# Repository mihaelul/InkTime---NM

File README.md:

# InkTime - E-Paper Smartwatch Hardware Design

## 1. System Block Diagram
*This diagram illustrates the main hardware modules and their data/power connections to the central processing unit.*

```mermaid
graph TD

    ANTENNA[ANTENNA] ---|RF| SOC[nRF52840 <br> SoC]
    
    %% Peripherals and Interfaces
    SOC ---|I2C| IMU[IMU <br> SENSOR]
    SOC ---|SPI| EPD[E-PAPER <br> DISPLAY]
    SOC ---|PWM| SHAKER[SHAKER]
    SOC ---|GPIO| BTN[3X <br> BUTTON]
    SOC ---|SWD| DEBUG[DEBUG <br> SWD]

    USB[USB-C <br> CONNECTOR] ---|VUSB| CHARGER[CHARGER IC]
    CHARGER --- BATTERY[LI-PO BATTERY]
    CHARGER --- VREG[RT6160 <br> VOLTAGE <br> REGULATOR]
    BATTERY ---|VBAT| VREG

    %% 3V3 Power Rails
    VREG ---|3V3| IMU
    VREG ---|3V3| EPD
    VREG ---|3V3| SHAKER
```

## 1. Bill of Materials (BOM)

| Component | JLC Part # | Package | Description | Datasheet |
| :--- | :--- | :--- | :--- | :--- |
| **J1** | C122434 | SMD,P=0.5mm,Surface Mount，Right Angle | FFC & FPC Connectors 0.5mm FPC RA SMT Dual Contact 24Ckt | [datasheet](https://octopart.com/datasheet/tag-connect/TC2030-IDC) |
| **L1, L2, L3** | C12669 | 402 | Generic chip inductor | [datasheet](https://www.lcsc.com/datasheet/C12669.pdf) |
| **L5** | C1329646 | SMD,4.8x4.8mm | 1.6A 1.6A 4.7uH 41.4mΩ AEC-Q200 ±30% SMD,4.8x4.8mm Power Inductors ROHS | [datasheet](https://wmsc.lcsc.com/wmsc/upload/file/pdf/v2/lcsc/2304140030_BOURNS-SRR4828A-4R7Y_C1329646.pdf) |
| **IC3** | C189517 | LGA-12(2x2) | Accelerometers Triaxial low-g 12bit Acceleration Sensor | [datasheet](https://files.pine64.org/doc/datasheet/pinetime/BST-BMA421-FL000.pdf) |
| **Q1** | C2564 | TO-220AB | -55℃~+175℃ 1 P-Channel 180nC@10V 200W 20mΩ@10V 3.4nF 4V 55V 640pF 74A P-Channel TO-220AB MOSFETs ROHS | [datasheet](https://files.pine64.org/doc/datasheet/pinetime/BST-BMA421-FL000.pdf) |
| **U3** | C2682616 | DFN-8-EP(2x2) | -40℃~+85℃ 1 2.5V~4.5V 3uA I2C Lithium Battery DFN-8-EP(2x2) Battery Management ROHS | [datasheet](https://www.analog.com/en/products/max17048.html?ADICID=synd_ww_portfolio_pi_octopart_na_2024) |
| **ANT1** | C2917717 | 1206 | -45℃~+125℃ 0.5dBi 1.3mm 1.6mm 100MHz 2.45GHz 2W 3.2mm 50Ω Patch Antenna 1206 Antennas ROHS | [datasheet](https://www.alldatasheet.com/datasheet-pdf/pdf/348957/JOHANSON/2450AT18B100.html) |
| **D3** | C2969755 | SOT-23-6L | Low Cap. ESD Protection Auto SOT-23-6 STMicroelectronics USBLC6-2SC6Y, Dual Uni-Directional TVS Diode Array, 6-Pin SOT-23 | [datasheet](https://octopart.com/datasheet/stmicroelectronics/USBLC6-2SC6Y) |
| **X2** | C32346 | SMD3215-2P | -40℃~+85℃ 12.5pF 32.768kHz 70kΩ Crystal Oscillator ±20ppm SMD3215-2P Crystals ROHS | [datasheet](https://www.lcsc.com/datasheet/C32346.pdf) |
| **U1** | C3606653 | QFN-48(6x6) | nRF52840 | [datasheet](https://octopart.com/datasheet/nordic-semiconductor/NRF52840-QIAA-T) |
| **IC1** | C3682423 | DSBGA-8(1.1x1.6) | Charger IC Lithium Ion/Polymer, Lithium Iron Phosphate 8-DSBGA (1.6x1.1) | [datasheet](https://www.alldatasheet.com/datasheet-pdf/pdf/1359210/TI/BQ25180YBGR.html) |
| **R17-R18, R1_EP_DR, R1_USB, R2-R5, R7-R9, R_PWR_EPD, R_TYPE_SEL** | C3920633 | 0201 | 7.68k 0201 Thin Film Surface Mount Fixed Resistor +/-0.5% 870.031W CPF0201D7K68C1 |  |
| **Q3** | C469327 | SOT-323 | MOSFET N-Ch 30V 1.5A TrenchFET SC70 Vishay Si1308EDL-T1-GE3 N-channel MOSFET Transistor, 1.5 A, 30 V, 3-Pin SC-70 | [datasheet](https://4donline.ihs.com/images/VipMasterIC/IC/VISH/VISH-S-A0000692786/VISH-S-A0000692786-1.pdf?hkey=6D3A4C79FDBF58556ACFDE234799DDF0) |
| **SW_DN, SW_ENT, SW_UP** | C569760 | SMD,3.9x2.9mm | -40℃~+85℃ 1.6N 1.6mm 15V 2.9mm 20mA 3.9mm 500,000 Cycles IP67 J-Lead Rectangular Button SPST Surface Mount White With Bracket | [datasheet](https://wmsc.lcsc.com/wmsc/upload/file/pdf/v2/lcsc/2301111010_PANASONIC-EVPAKE31A_C569760.pdf) |
| **L7** | C5832368 | 1008 | 13mΩ 470nH 6.5A 7.5A ±20% 1008 Power Inductors ROHS | [datasheet](https://www.lcsc.com/datasheet/C5832368.pdf?spm=wm.sxq.inf.ggs&lcsc_vid=RQcLUgVXFFNXXwFeQQJaUQVXFgRWA1xUFlcIVABQQQQxVlNRQVZXXlBXQ1VfUjsOAxUeFF5JWBYZEEoBGA4JCwFIFA4DSA%3D%3D) |
| **IC9** | C7065276 | WLCSP-15B(2.3x1.4) | Buck-Boost Regulator Positive Output Step-Up/Step-Down I2C DC-DC Controller IC 15-WL-CSP | [datasheet](https://www.alldatasheet.com/datasheet-pdf/pdf/1709403/RICHTEK/RT6160AWSC.html) |
| **J4** | C709357 | SMD | 16P Female Surface Mount, Right Angle Type-C SMD USB Connectors ROHS | [datasheet](https://www.lcsc.com/datasheet/C709357.pdf) |
| **IC2** | C81079 | DSBGA-9 | Haptic Driver for ERM/LRA with Built-In Library and Smart Loop Architecture | [datasheet](https://www.alldatasheet.com/datasheet-pdf/pdf/489356/TI/DRV2605.html) |
| **D2, D4, D5** | C82046 | SOD-123 | ON SEMICONDUCTOR - MBR0530 - DIODE, SCHOTTKY, 0.5A, 30V, SOD-123 | [datasheet](https://www.lcsc.com/datasheet/C82046.pdf) |
| **X1** | C9009 | SMD3225-4P | 32MHz Crystal Oscillator ±10ppm ±20ppm SMD3225-4P Crystals ROHS | [datasheet](https://www.lcsc.com/datasheet/C9009.pdf) |
| **J2** | C90533 | P=1mm | CABLE ADAPTER 6 POS | https://octopart.com/datasheet/tag-connect/TC2030-IDC |
| **C6, C14, C15, C20, C21, C24, C25, C33, C39** | C9900179830 | 0402 | Generic chip capacitor |  [datasheet](https://octopart.com/datasheet/kyocera-avx/0402YC104KAT2A) |
| **EPD_C1 - EPD_C12** | C9900179830 | 0402 | Generic chip capacitor | [datasheet](https://octopart.com/datasheet/kyocera-avx/0402YC104KAT2A) |
| **C1, C2, C3, C4, C5, C7, C8, C9, C10, C11, C12, C13, C16, C17, C18, C19** | C9900156064 | 0201 | Generic chip capacitor | [datasheet](https://www.we-online.com/components/products/datasheet/885012104003.pdf?srsltid=AfmBOorfnt8kPvUhmauvZrnnkcX57K9BGcdXKzCLOcfskhqns-UBbXMT) |

## 3. Hardware Functionality & Specifications

The InkTime hardware architecture is centered around a **30-day battery life** target, utilizing an ultra-low-power interrupt-driven design.

### 1. Core Processing & Connectivity
* **SoC:** **nRF52840** (ARM Cortex-M4F) handles BLE 5.0 connectivity and main system logic.
* **Clocking:** 32MHz crystal for high-speed operations and a 32.768kHz crystal for accurate RTC timekeeping during sleep.
* **Programming:** Integrated **SWD** interface accessible via a Tag-Connect TC2030 footprint.

### 2. Power Management System
* **Battery:** **250mAh LiPo** (AKYGA LP502030) providing the primary power source.
* **Charging:** **BQ25180** charger IC manages USB charging via I2C and signals MCU on power events.
* **Regulation:** **RT6160** Buck-Boost converter stabilizes the 3.3V system rail across the full battery voltage range.
* **Monitoring:** **MAX17048** Fuel Gauge tracks battery State of Charge (SoC) via I2C with precision.

### 3. Display & User Interface
* **Display:** **1.54" E-Paper** (200x200) connected via **SPI**.
* **Power Gating:** An **SI2301 P-FET** switch is used to completely cut power to the display circuit between refreshes to eliminate leakage.
* **Refresh Policy:** Partial refresh is triggered once per minute to minimize energy consumption.
* **Input:** Three side-mounted tactile buttons (Up, Down, Enter/Esc) configured with internal pull-ups and wake-on-low interrupts.

### 4. Sensors & Haptics (I2C Bus)
* **Motion Sensing:** **BMA421** Accelerometer provides step counting and gesture wake-up functionality.
* **Haptic Feedback:** **DRV2605L** driver controls an **ERM vibration motor** to provide tactile notifications.
* **Efficiency:** Both modules are strictly managed; the haptic driver is disabled via an Enable pin when not in use.

### 5. Energy Profile
* **Sleep Current:** System spends >95% of time in deep sleep with peripherals powered down.
* **Active Peaks:** Energy is primarily consumed during BLE transfers and 1-minute display updates (~8mAs per update).

## 4. Detailed Pinout & Design Justification (nRF52840)

The pin mapping for the nRF52840 was optimized for **Power Efficiency**, **Signal Integrity (RF)**, and **PCB Routing** (minimizing via count and crossing traces).

### Communication & Power Control
| Pin | Net Name | Component | Justification |
| :--- | :--- | :--- | :--- |
| **ANT** | RF_OUT | Ceramic Antenna | Dedicated RF output requiring a 50Ω matched trace to the antenna network. |
| **P0.06 / P0.07** | I2C_SDA / SCL | Shared I2C Bus | Shared bus for BMA421, MAX17048, DRV2605L, and BQ25180 to conserve pins and simplify routing. |
| **P0.02 / P0.03** | EPD_SCK / MOSI | E-Paper (SPI) | High-speed SPI clock and data for the display. |
| **P0.05** | EPD_CS | E-Paper (SPI) | Chip Select to keep the EPD controller inactive when the bus is shared. |
| **P0.15 / P0.16** | EPD_DC / RST | E-Paper Control | Dedicated pins for Data/Command toggling and hardware reset. |
| **P0.17** | EPD_BUSY | E-Paper Status | Monitors internal state, allowing the MCU to sleep during EPD refresh cycles. |
| **P1.01** | PWR_EPD | P-FET Gate (Q4) | **Critical:** High-side power gating to physically cut power to the EPD, eliminating standby leakage. |

### User Input & Interrupts
| Pin | Net Name | Component | Justification |
| :--- | :--- | :--- | :--- |
| **P0.13 / P0.14** | SW_UP / SW_DN | Nav Buttons | Configured with internal pull-ups. Supports "Wake-on-Low" to wake the SoC from deep sleep. |
| **P1.00** | SW_ENT | Enter Button | Placed on Port 1 to simplify physical trace routing to the right edge of the PCB. |
| **P0.08** | IMU_INT1 | BMA421 (INT) | Primary interrupt for step detection, waking the MCU only when necessary. |
| **P0.12** | HAPTIC_EN | DRV2605L | Completely disables the haptic driver IC when inactive to save microamps of quiescent current. |

### System Timing & Debug
| Pin | Net Name | Component | Justification |
| :--- | :--- | :--- | :--- |
| **XC1 / XC2** | 32M_XTAL | 32MHz Crystal | Essential for BLE radio operation and high-accuracy internal timing. |
| **XL1 / XL2** | 32K_XTAL | 32.768kHz Crystal | Low-power clock for the RTC, keeping time while the system is in deep sleep. |
| **SWDIO / CLK**| SWD_DATA / CLK | Tag-Connect J2 | Standard ARM programming interface, placed near the edge for easy access. |

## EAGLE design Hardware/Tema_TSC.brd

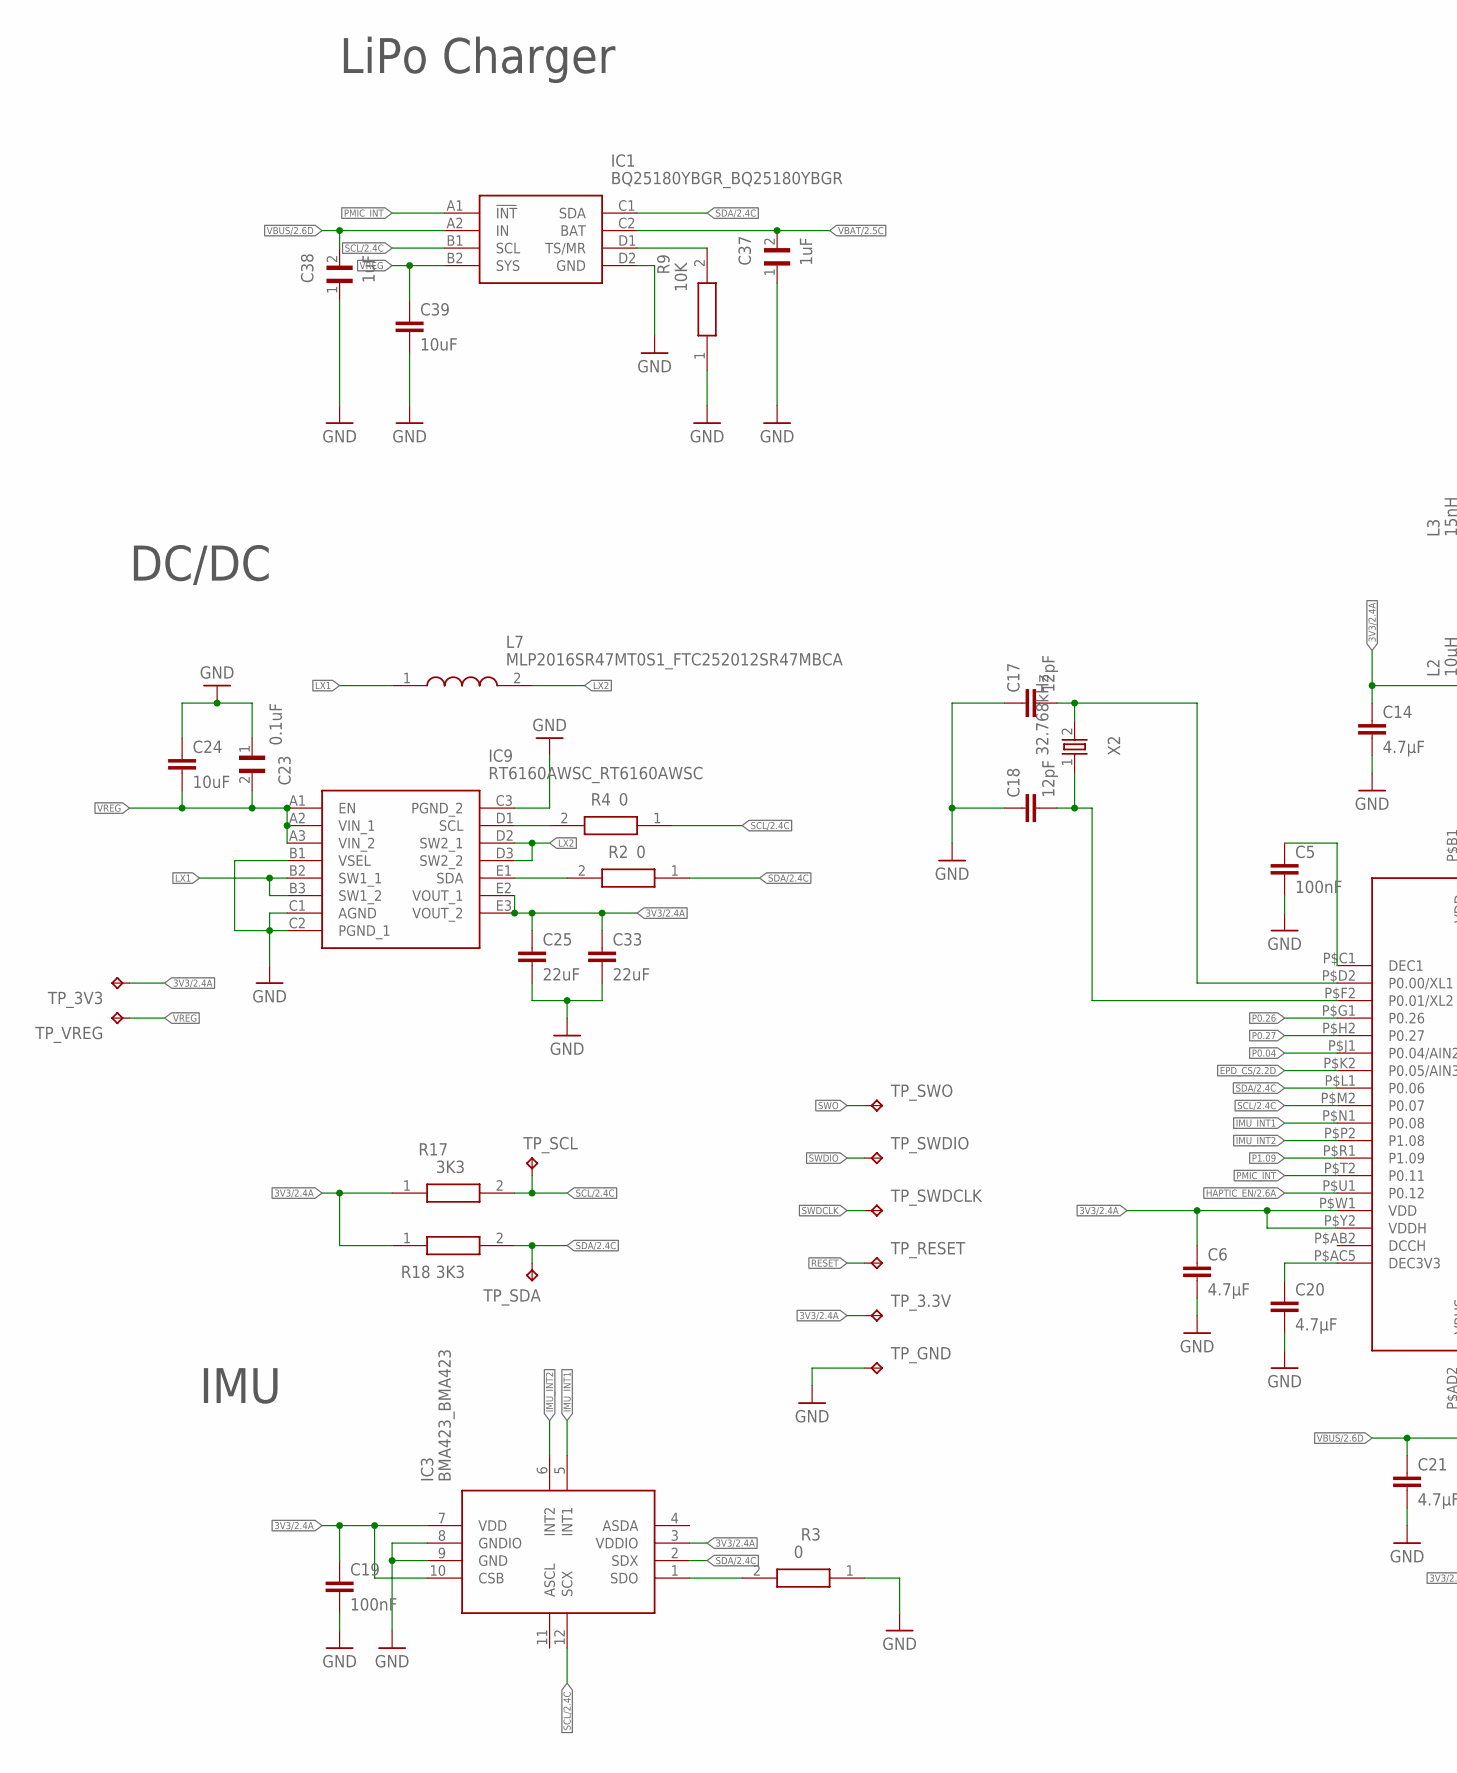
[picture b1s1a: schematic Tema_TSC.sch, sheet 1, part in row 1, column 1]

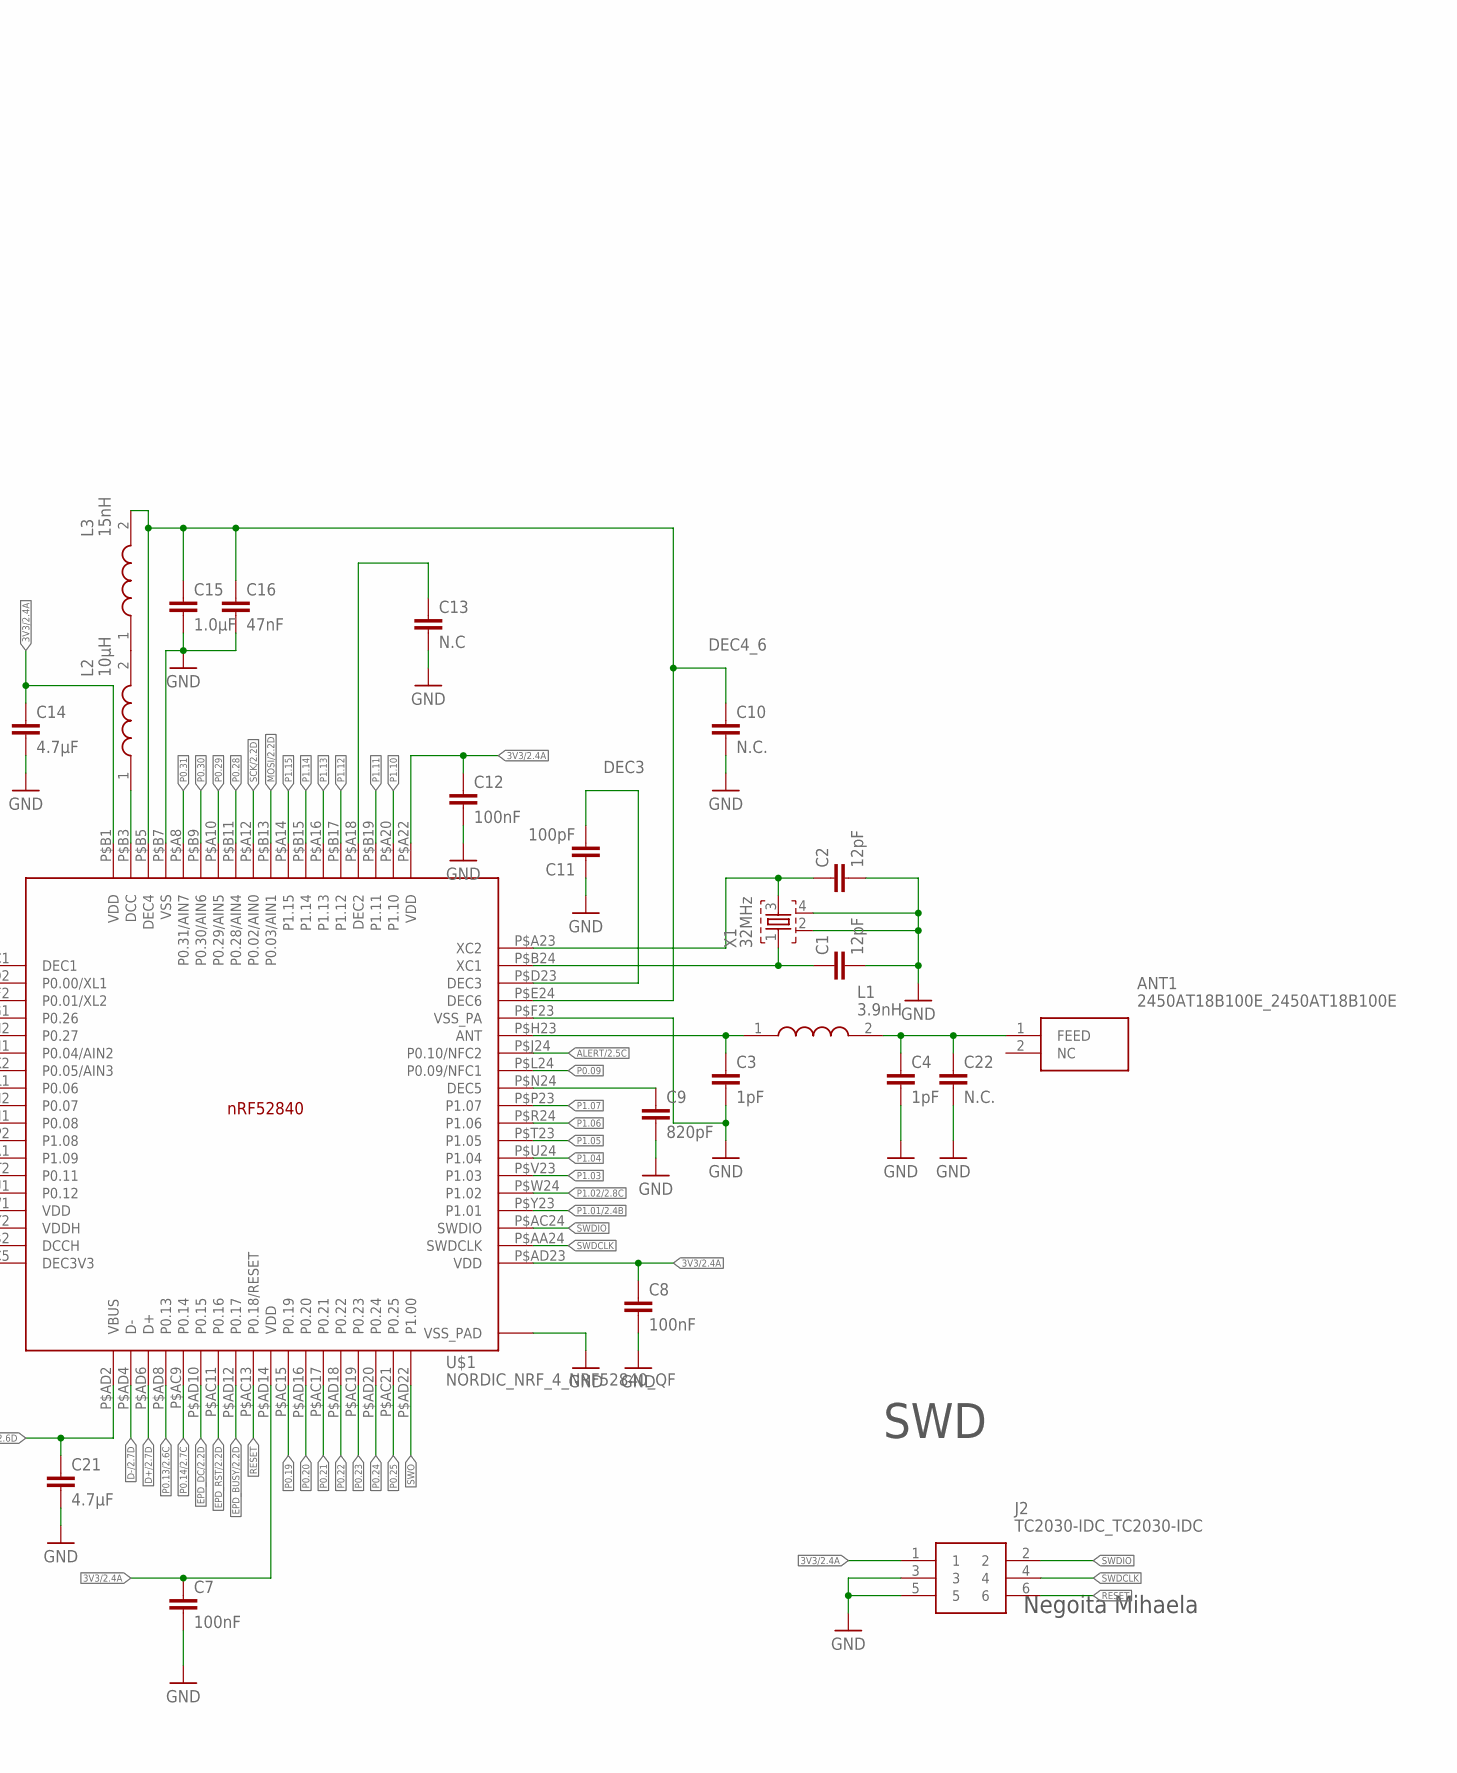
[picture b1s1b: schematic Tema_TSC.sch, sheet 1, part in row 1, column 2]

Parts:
ANT1: 2450AT18B100E_2450AT18B100E; 2450AT18B100E_ANTC3216X140N
C1, C2: 12pF; NORDIC_NRF_3_RESC0201_L
C3, C4: 1pF; NORDIC_NRF_3_RESC0201_L
C5, C12, C19: 100nF; NORDIC_NRF_3_RESC0201_N
C6, C14, C20, C21: 4.7µF; NORDIC_NRF_3_RESC0402_N
C7, C8: 100nF; NORDIC_NRF_3_RESC0201_L
C9: 820pF; NORDIC_NRF_3_RESC0201_L
C10, C22: N.C.; NORDIC_NRF_3_RESC0201_L
C11: 100pF; NORDIC_NRF_3_RESC0201_L
C13: N.C; NORDIC_NRF_3_RESC0201_N
C15: 1.0µF; NORDIC_NRF_3_RESC0402_N
C16: 47nF; NORDIC_NRF_3_RESC0201_N
C17, C18: 12pF; NORDIC_NRF_3_RESC0201_N
C23: 0.1uF; GRM011R60J152KE01L_2_CAPC0201X13N
C24, C39: 10uF; NORDIC_NRF_3_RESC0402_N
C25, C33: 22uF; NORDIC_NRF_3_RESC0402_N
C37, C38: 1uF; GRM011R60J152KE01L_2_CAPC0201X13N
IC1: BQ25180YBGR_BQ25180YBGR; BQ25180YBGR_BGA8C40P2X4_100X155X50
IC3: BMA423_BMA423
IC9: RT6160AWSC_RT6160AWSC; RT6160AWSC_BGA15C40P3X5_140X230X60
J2: TC2030-IDC_TC2030-IDC; TC2030-IDC_TC2030IDC
L1: 3.9nH; MLP2016SR47MT0S1_INDC2016X100N
L2: 10µH; MLP2016SR47MT0S1_INDC2016X100N
L3: 15nH; MLP2016SR47MT0S1_INDC2016X100N
L7: MLP2016SR47MT0S1_FTC252012SR47MBCA; MLP2016SR47MT0S1_INDC2016X100N
R2, R3, R4: 0; CPF0201D7K68C1_0201
R9: 10K; CPF0201D7K68C1_0201
R17, R18: 3K3; CPF0201D7K68C1_0201
TP_3.3V, TP_3V3: HECTOR_WATCH_1_TPTP20R; HECTOR_WATCH_1_TP20R
TP_GND: HECTOR_WATCH_1_TPTP20R; HECTOR_WATCH_1_TP20R
TP_RESET: HECTOR_WATCH_1_TPTP20R; HECTOR_WATCH_1_TP20R
TP_SCL: HECTOR_WATCH_1_TPTP20R; HECTOR_WATCH_1_TP20R
TP_SDA: HECTOR_WATCH_1_TPTP20R; HECTOR_WATCH_1_TP20R
TP_SWDCLK: HECTOR_WATCH_1_TPTP20R; HECTOR_WATCH_1_TP20R
TP_SWDIO: HECTOR_WATCH_1_TPTP20R; HECTOR_WATCH_1_TP20R
TP_SWO: HECTOR_WATCH_1_TPTP20R; HECTOR_WATCH_1_TP20R
TP_VREG: HECTOR_WATCH_1_TPTP20R; HECTOR_WATCH_1_TP20R
U$1: NORDIC_NRF_4_NRF52840_QF; NORDIC_NRF_4_AQFN50P700X700X85_HS-74N
X1: 32MHz; NORDIC_NRF_BT-XTAL_2016_N
X2: 32.768kHz; NORDIC_NRF_1_XTAL_3215_N

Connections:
3V3/2.4A: C6.1, C7.1, C8.1, C12.1, C14.1, C19.1, C25.1, C33.1, IC3.3 (VDDIO), IC3.7 (VDD), IC3.10 (CSB), IC9.E2 (VOUT_1), IC9.E3 (VOUT_2), J2.1, R17.1, R18.1, TP_3.3V.TP, TP_3V3.TP, U$1.P$A22 (VDD), U$1.P$AD14 (VDD), U$1.P$AD23 (VDD), U$1.P$B1 (VDD), U$1.P$W1 (VDD), U$1.P$Y2 (VDDH)
ALERT/2.5C: U$1.P$J24 (P0.10/NFC2)
D+/2.7D: U$1.P$AD6 (D+)
D-/2.7D: U$1.P$AD4 (D-)
DEC3: C11.2, U$1.P$D23 (DEC3)
DEC4_6: C10.1, C15.1, C16.1, L3.2, U$1.P$B5 (DEC4), U$1.P$E24 (DEC6)
EPD_BUSY/2.2D: U$1.P$AD12 (P0.17)
EPD_CS/2.2D: U$1.P$K2 (P0.05/AIN3)
EPD_DC/2.2D: U$1.P$AD10 (P0.15)
EPD_RST/2.2D: U$1.P$AC11 (P0.16)
GND: C1.2, C2.2, C3.2, C4.2, C5.2, C6.2, C7.2, C8.2, C9.2, C10.2, C11.1, C12.2, C13.2, C14.2, C15.2, C16.2, C17.1, C18.1, C19.2, C20.2, C21.2, C22.2, C23.1, C24.1, C25.2, C33.2, C37.1, C38.1, C39.2, IC1.D2 (GND), IC3.8 (GNDIO), IC3.9 (GND), IC9.B1 (VSEL), IC9.C1 (AGND), IC9.C2 (PGND_1), IC9.C3 (PGND_2), J2.3, J2.5, R3.1, R9.1, TP_GND.TP, U$1.P$74 (VSS_PAD), U$1.P$75 (VSS_PAD), U$1.P$76 (VSS_PAD), U$1.P$77 (VSS_PAD), U$1.P$78 (VSS_PAD), U$1.P$79 (VSS_PAD), U$1.P$80 (VSS_PAD), U$1.P$81 (VSS_PAD), U$1.P$82 (VSS_PAD), U$1.P$83 (VSS_PAD), U$1.P$84 (VSS_PAD), U$1.P$85 (VSS_PAD), U$1.P$86 (VSS_PAD), U$1.P$87 (VSS_PAD), U$1.P$88 (VSS_PAD), U$1.P$89 (VSS_PAD), U$1.P$90 (VSS_PAD), U$1.P$B7 (VSS), U$1.P$F23 (VSS_PA), X1.2, X1.4; also elsewhere on the board
HAPTIC_EN/2.6A: U$1.P$U1 (P0.12)
IMU_INT1: IC3.5 (INT1), U$1.P$N1 (P0.08)
IMU_INT2: IC3.6 (INT2), U$1.P$P2 (P1.08)
LX1: IC9.B2 (SW1_1), IC9.B3 (SW1_2), L7.1
LX2: IC9.D2 (SW2_1), IC9.D3 (SW2_2), L7.2
MOSI/2.2D: U$1.P$B13 (P0.03/AIN1)
unnamed: C2.1, U$1.P$A23 (XC2), X1.3
unnamed: C1.1, U$1.P$B24 (XC1), X1.1
unnamed: C3.1, L1.1, U$1.P$H23 (ANT)
unnamed: L2.1, U$1.P$B3 (DCC)
unnamed: L2.2, L3.1
unnamed: ANT1.1 (FEED), C4.1, C22.1, L1.2
unnamed: C20.1, U$1.P$AC5 (DEC3V3)
unnamed: C5.1, U$1.P$C1 (DEC1)
unnamed: C17.2, U$1.P$D2 (P0.00/XL1), X2.2
unnamed: C18.2, U$1.P$F2 (P0.01/XL2), X2.1
unnamed: C13.1, U$1.P$A18 (DEC2)
unnamed: IC9.D1 (SCL), R4.2
unnamed: IC9.E1 (SDA), R2.2
unnamed: IC1.D1 (TS/MR), R9.2
unnamed: IC3.1 (SDO), R3.2
unnamed: C9.1, U$1.P$N24 (DEC5)
P0.04: U$1.P$J1 (P0.04/AIN2)
P0.09: U$1.P$L24 (P0.09/NFC1)
P0.13/2.6C: U$1.P$AD8 (P0.13)
P0.14/2.7C: U$1.P$AC9 (P0.14)
P0.19: U$1.P$AC15 (P0.19)
P0.20: U$1.P$AD16 (P0.20)
P0.21: U$1.P$AC17 (P0.21)
P0.22: U$1.P$AD18 (P0.22)
P0.23: U$1.P$AC19 (P0.23)
P0.24: U$1.P$AD20 (P0.24)
P0.25: U$1.P$AC21 (P0.25)
P0.26: U$1.P$G1 (P0.26)
P0.27: U$1.P$H2 (P0.27)
P0.28: U$1.P$B11 (P0.28/AIN4)
P0.29: U$1.P$A10 (P0.29/AIN5)
P0.30: U$1.P$B9 (P0.30/AIN6)
P0.31: U$1.P$A8 (P0.31/AIN7)
P1.01/2.4B: U$1.P$Y23 (P1.01)
P1.02/2.8C: U$1.P$W24 (P1.02)
P1.03: U$1.P$V23 (P1.03)
P1.04: U$1.P$U24 (P1.04)
P1.05: U$1.P$T23 (P1.05)
P1.06: U$1.P$R24 (P1.06)
P1.07: U$1.P$P23 (P1.07)
P1.09: U$1.P$R1 (P1.09)
P1.10: U$1.P$A20 (P1.10)
P1.11: U$1.P$B19 (P1.11)
P1.12: U$1.P$B17 (P1.12)
P1.13: U$1.P$A16 (P1.13)
P1.14: U$1.P$B15 (P1.14)
P1.15: U$1.P$A14 (P1.15)
PMIC_INT: IC1.A1 (!INT), U$1.P$T2 (P0.11)
RESET: J2.6, TP_RESET.TP, U$1.P$AC13 (P0.18/RESET)
SCK/2.2D: U$1.P$A12 (P0.02/AIN0)
SCL/2.4C: IC1.B1 (SCL), IC3.12 (SCX), R4.1, R17.2, TP_SCL.TP, U$1.P$M2 (P0.07)
SDA/2.4C: IC1.C1 (SDA), IC3.2 (SDX), R2.1, R18.2, TP_SDA.TP, U$1.P$L1 (P0.06)
SWDCLK: J2.4, TP_SWDCLK.TP, U$1.P$AA24 (SWDCLK)
SWDIO: J2.2, TP_SWDIO.TP, U$1.P$AC24 (SWDIO)
SWO: TP_SWO.TP, U$1.P$AD22 (P1.00)
VBAT/2.5C: C37.2, IC1.C2 (BAT)
VBUS/2.6D: C21.1, C38.2, IC1.A2 (IN), U$1.P$AD2 (VBUS)
VREG: C23.2, C24.2, C39.1, IC1.B2 (SYS), IC9.A1 (EN), IC9.A2 (VIN_1), IC9.A3 (VIN_2), TP_VREG.TP

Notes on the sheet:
LiPo Charger
DC/DC
IMU
SWD
Negoita Mihaela

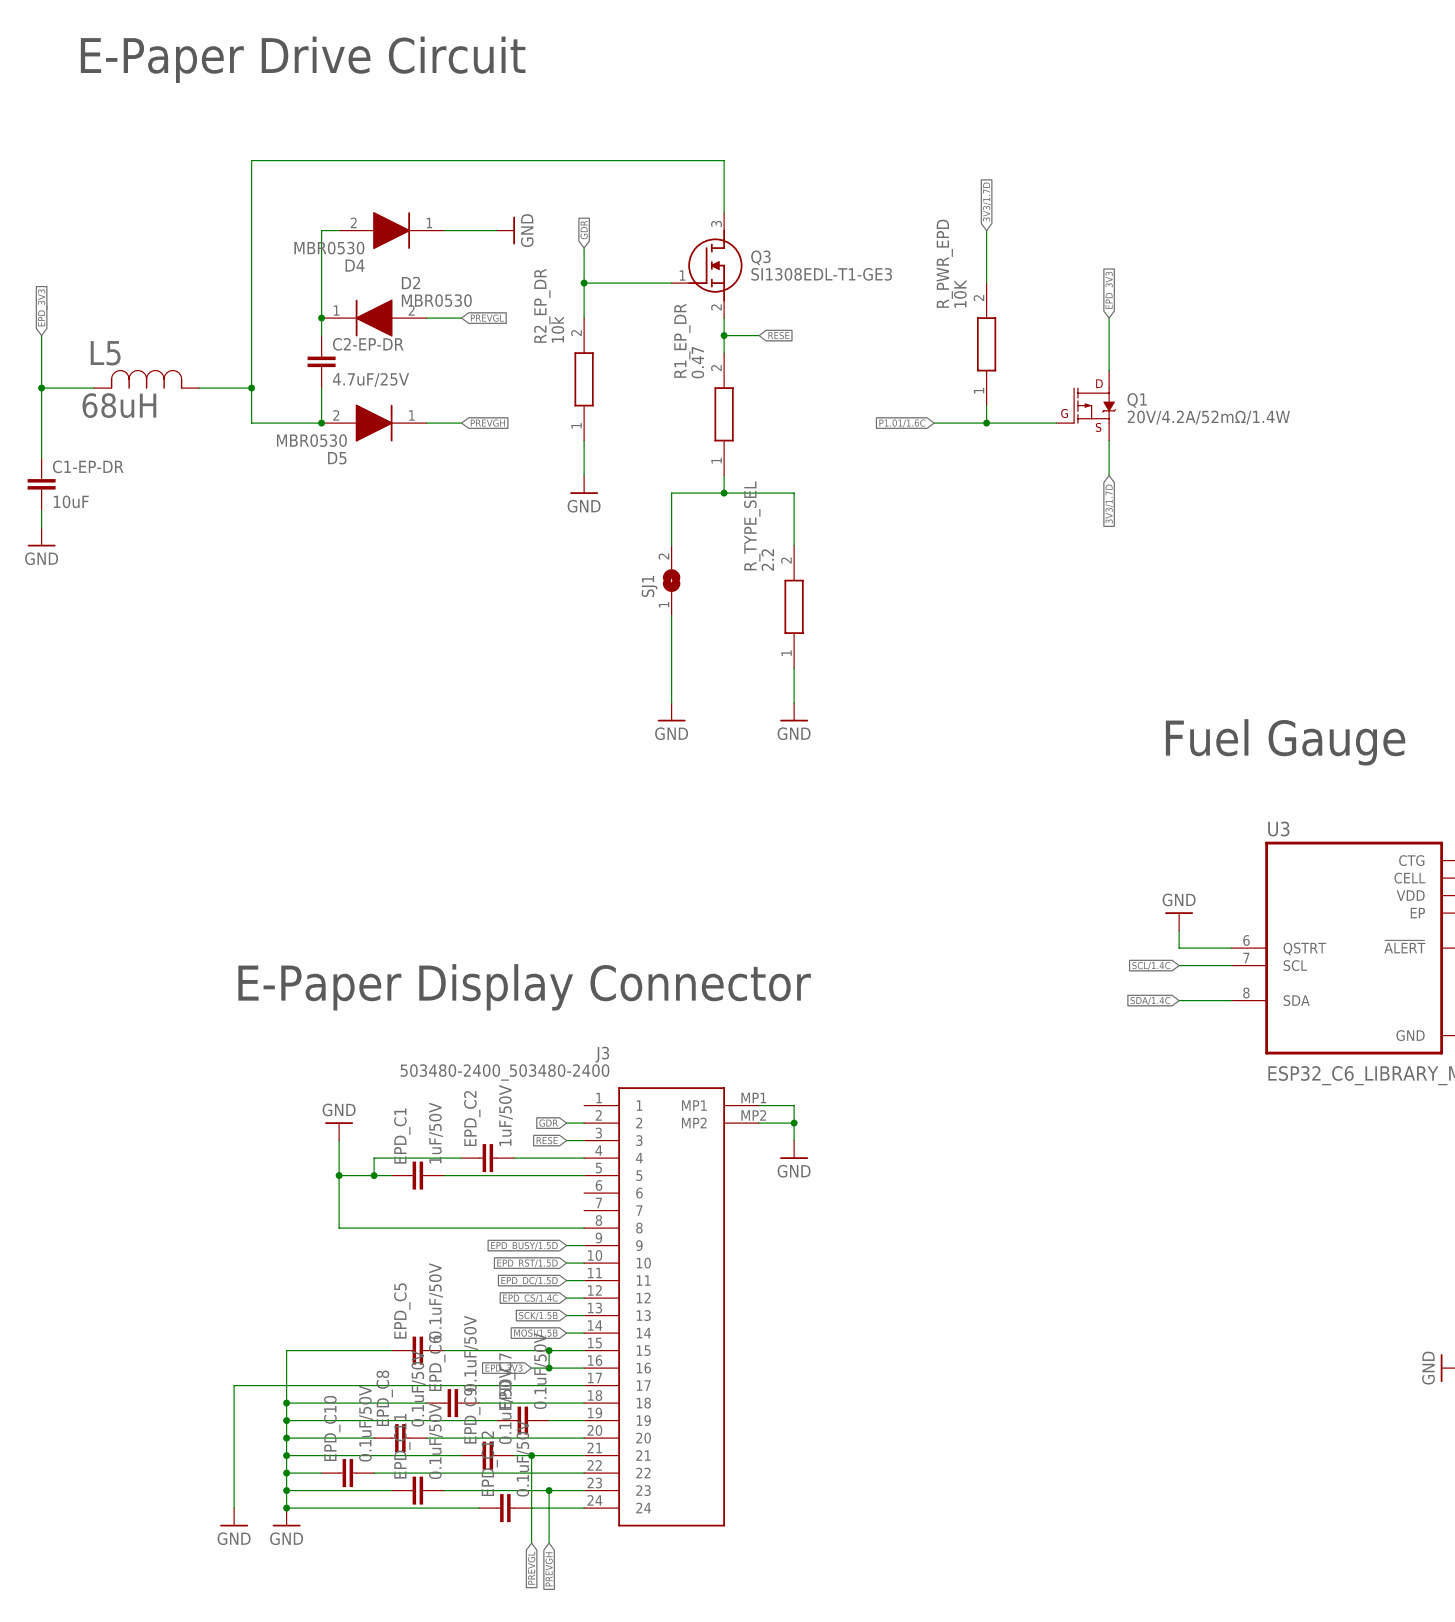
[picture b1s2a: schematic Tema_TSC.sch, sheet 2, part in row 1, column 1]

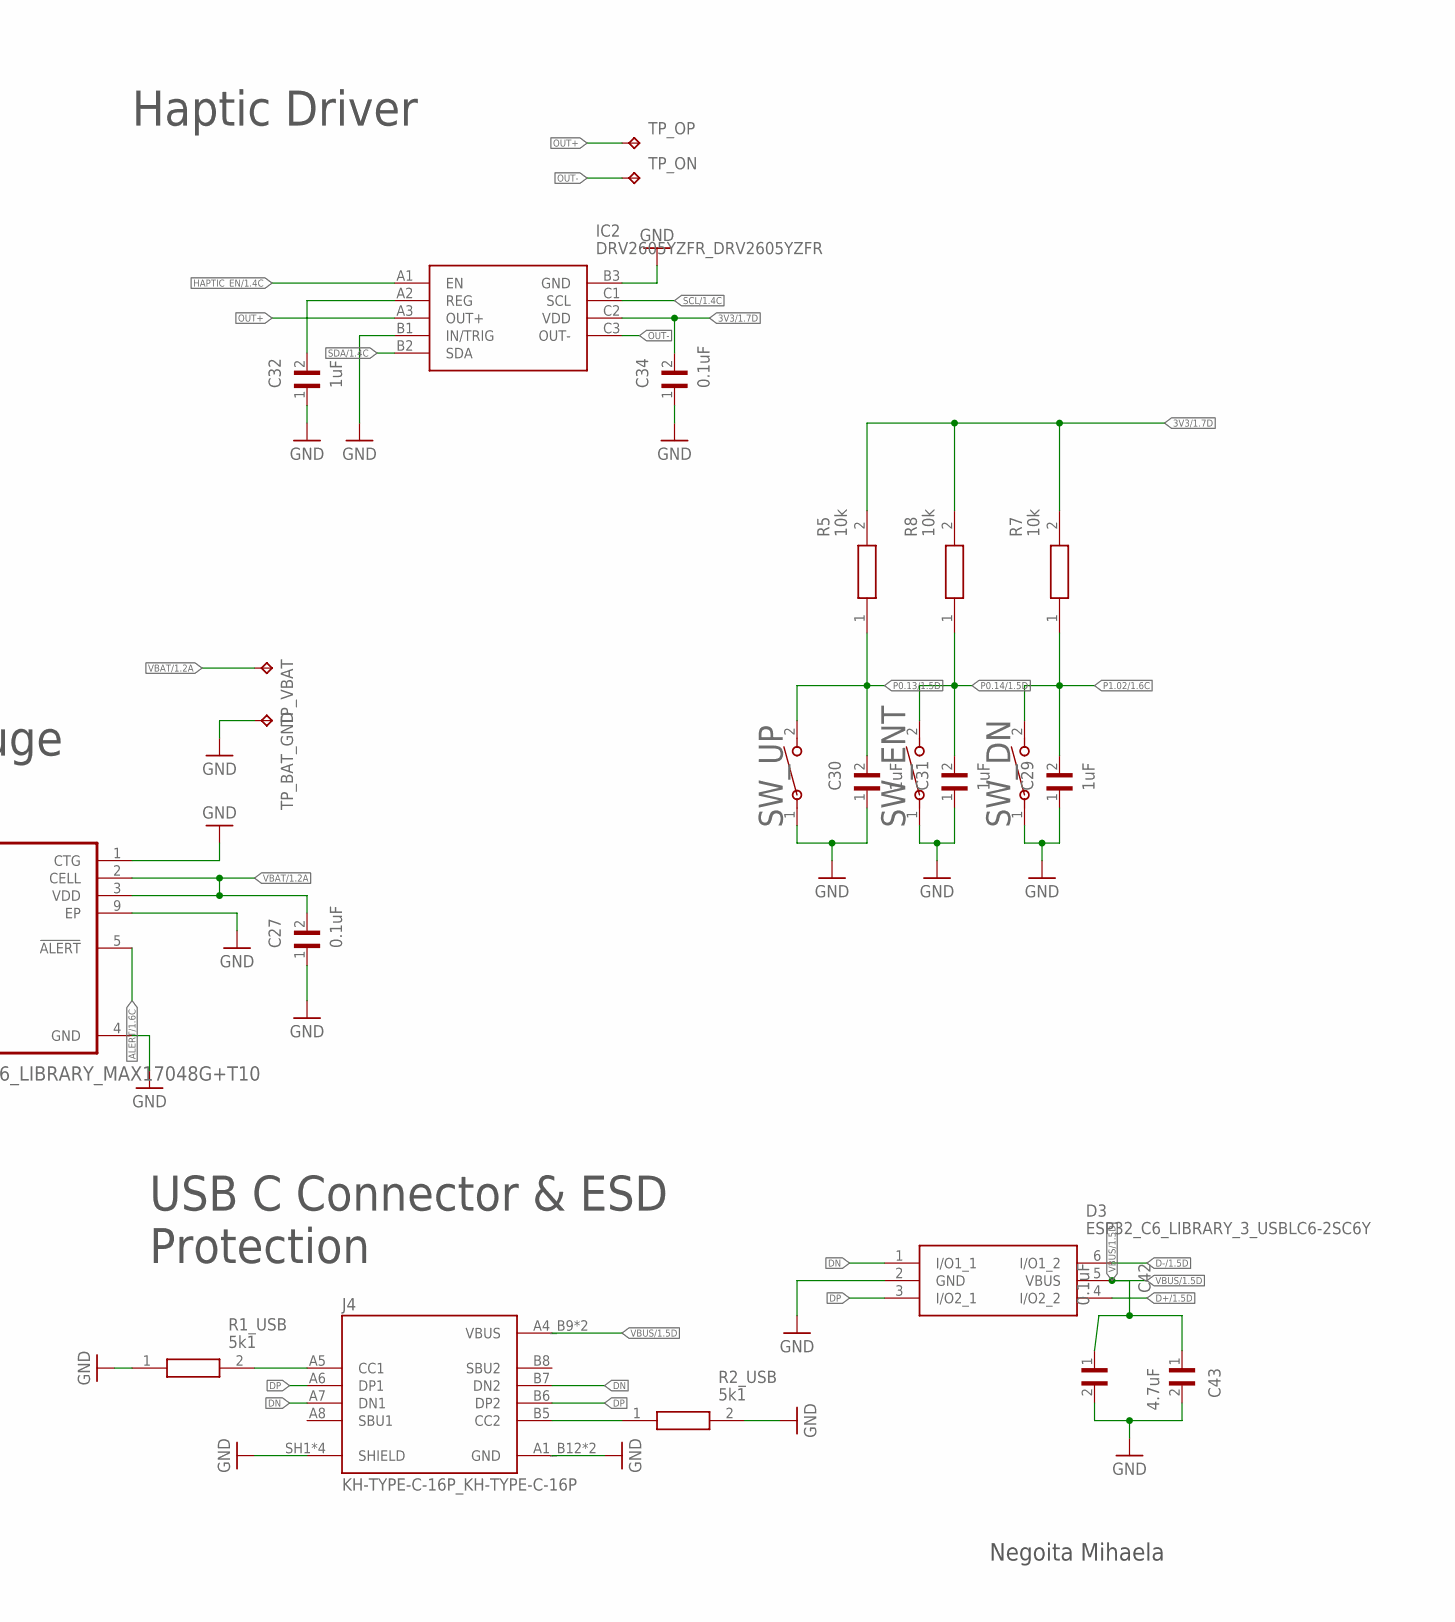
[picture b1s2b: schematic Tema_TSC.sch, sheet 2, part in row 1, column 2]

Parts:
C1-EP-DR: 10uF; NORDIC_NRF_3_RESC0402_N
C2-EP-DR: 4.7uF/25V; NORDIC_NRF_3_RESC0402_N
C27, C34, C42: 0.1uF; GRM011R60J152KE01L_2_CAPC0201X13N
C29, C30, C31, C32: 1uF; GRM011R60J152KE01L_2_CAPC0201X13N
C43: 4.7uF; GRM011R60J152KE01L_2_CAPC0201X13N
D2, D4, D5: MBR0530; ESP32_C6_LIBRARY_5_SOD3716X135N
D3: ESP32_C6_LIBRARY_3_USBLC6-2SC6Y; ESP32_C6_LIBRARY_3_SOT95P280X145-6N
EPD_C1, EPD_C2: 1uF/50V; NORDIC_NRF_3_RESC0402_N
EPD_C5, EPD_C6, EPD_C7, EPD_C8, EPD_C9, EPD_C10, EPD_C11, EPD_C12: 0.1uF/50V; NORDIC_NRF_3_RESC0402_N
IC2: DRV2605YZFR_DRV2605YZFR; DRV2605YZFR_BGA9C50P3X3_144X144X62
J3: 503480-2400_503480-2400; 503480-2400_5034802400
J4: KH-TYPE-C-16P_KH-TYPE-C-16P; KH-TYPE-C-16P_KINGHELM_KH-TYPE-C-16P
L5: 68uH; ESP32_C6_LIBRARY_2_IND_4828-WE-TPC_WRE
Q1: 20V/4.2A/52mΩ/1.4W; ESP32_C6_LIBRARY_4_ESP32_C6_LIBRARY_4_ESP32_C6_LIBRARY_4_ES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
Q3: SI1308EDL-T1-GE3; ESP32_C6_LIBRARY_6_SOT65P210X110-3N
R1_EP_DR: 0.47; CPF0201D7K68C1_0201
R1_USB, R2_USB: 5k1; ERA-1AEB3401C_0201
R2_EP_DR, R5, R7, R8: 10k; CPF0201D7K68C1_0201
R_PWR_EPD: 10K; CPF0201D7K68C1_0201
R_TYPE_SEL: 2.2; CPF0201D7K68C1_0201
SJ1: ESP32_C6_LIBRARY_7_JUMPER_SJ
SW_DN: 2025-10-22_07-23-44_LIBRARY_EVP-AKE31ASW_EVP-AKE3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; 2025-10-22_07-23-44_LIBRARY_SW_EVP-AKE31A_PAN
SW_ENT: 2025-10-22_07-23-44_LIBRARY_EVP-AKE31ASW_EVP-AKE3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; 2025-10-22_07-23-44_LIBRARY_SW_EVP-AKE31A_PAN
SW_UP: 2025-10-22_07-23-44_LIBRARY_EVP-AKE31ASW_EVP-AKE3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; 2025-10-22_07-23-44_LIBRARY_SW_EVP-AKE31A_PAN
TP_BAT_GND: HECTOR_WATCH_1_TPTP20R; HECTOR_WATCH_1_TP20R
TP_ON: HECTOR_WATCH_1_TPTP20R; HECTOR_WATCH_1_TP20R
TP_OP: HECTOR_WATCH_1_TPTP20R; HECTOR_WATCH_1_TP20R
TP_VBAT: HECTOR_WATCH_1_TPTP20R; HECTOR_WATCH_1_TP20R
U3: ESP32_C6_LIBRARY_MAX17048G+T10; ESP32_C6_LIBRARY_SON50P200X200X80-9N

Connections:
ALERT/1.6C: U3.5 (!ALERT)
D+/1.5D: D3.4 (I/O2_2)
D-/1.5D: D3.6 (I/O1_2)
DN: D3.1 (I/O1_1), J4.A7 (DN1), J4.B7 (DN2)
DP: D3.3 (I/O2_1), J4.A6 (DP1), J4.B6 (DP2)
EPD_3V3: C1-EP-DR.1, EPD_C5.2, J3.15, J3.16, L5.2, Q1.3 (D)
EPD_BUSY/1.5D: J3.9
EPD_CS/1.4C: J3.12
EPD_DC/1.5D: J3.11
EPD_RST/1.5D: J3.10
GDR: J3.2, Q3.1 (G), R2_EP_DR.2
GND: C1-EP-DR.2, C27.1, C29.1, C30.1, C31.1, C32.1, C34.1, C42.2, C43.2, D3.2 (GND), D4.1 (K), EPD_C1.1, EPD_C2.1, EPD_C5.1, EPD_C6.1, EPD_C7.1, EPD_C8.1, EPD_C9.1, EPD_C10.1, EPD_C11.1, EPD_C12.1, IC2.B1 (IN/TRIG), IC2.B3 (GND), J3.8, J3.17, J3.MP1, J3.MP2, J4.A1_B12 (GND), J4.A12_B1 (GND), J4.SH1 (SHIELD), J4.SH2 (SHIELD), J4.SH3 (SHIELD), J4.SH4 (SHIELD), R1_USB.1, R2_EP_DR.1, R2_USB.2, R_TYPE_SEL.1, SJ1.1, SW_DN.1, SW_ENT.1, SW_UP.1, TP_BAT_GND.TP, U3.1 (CTG), U3.4 (GND), U3.6 (QSTRT), U3.9 (EP); also elsewhere on the board
HAPTIC_EN/1.4C: IC2.A1 (EN)
MOSI/1.5B: J3.14
unnamed 45: C2-EP-DR.1, D2.1 (K), D4.2 (A); also elsewhere on the board
unnamed 46: C2-EP-DR.2, D5.2 (A), L5.1, Q3.3 (D); also elsewhere on the board
unnamed: C32.2, IC2.A2 (REG)
unnamed: J4.A5 (CC1), R1_USB.2
unnamed: R1_EP_DR.1, R_TYPE_SEL.2, SJ1.2
unnamed: J4.B5 (CC2), R2_USB.1
unnamed: EPD_C2.2, J3.4
unnamed: EPD_C1.2, J3.5
unnamed: EPD_C6.2, J3.18
unnamed: EPD_C7.2, J3.19
unnamed: EPD_C8.2, J3.20
unnamed: EPD_C10.2, J3.22
OUT+: IC2.A3 (OUT+), TP_OP.TP
OUT-: IC2.C3 (OUT-), TP_ON.TP
P0.13/1.5D: C30.2, R5.1, SW_UP.2
P0.14/1.5D: C31.2, R8.1, SW_ENT.2
P1.01/1.6C: Q1.1 (G), R_PWR_EPD.1
P1.02/1.6C: C29.2, R7.1, SW_DN.2
PREVGH: D5.1 (K), EPD_C11.2, J3.23
RESE: J3.3, Q3.2 (S), R1_EP_DR.2
SCK/1.5B: J3.13
SCL/1.4C: IC2.C1 (SCL), U3.7 (SCL)
SDA/1.4C: IC2.B2 (SDA), U3.8 (SDA)
VBUS/1.5D: C42.1, C43.1, D3.5 (VBUS), J4.A4_B9 (VBUS), J4.A9_B4 (VBUS)

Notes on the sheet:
E-Paper Drive Circuit
Haptic Driver
E-Paper Display Connector
Fuel Gauge
USB C Connector & ESD Protection
Negoita Mihaela

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

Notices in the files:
parts and their libraries:
COPYRIGHT: Copyright (C) 2024 Ultra Librarian. All rights reserved.
COPYRIGHT: Copyright (C) 2025 Ultra Librarian. All rights reserved.
